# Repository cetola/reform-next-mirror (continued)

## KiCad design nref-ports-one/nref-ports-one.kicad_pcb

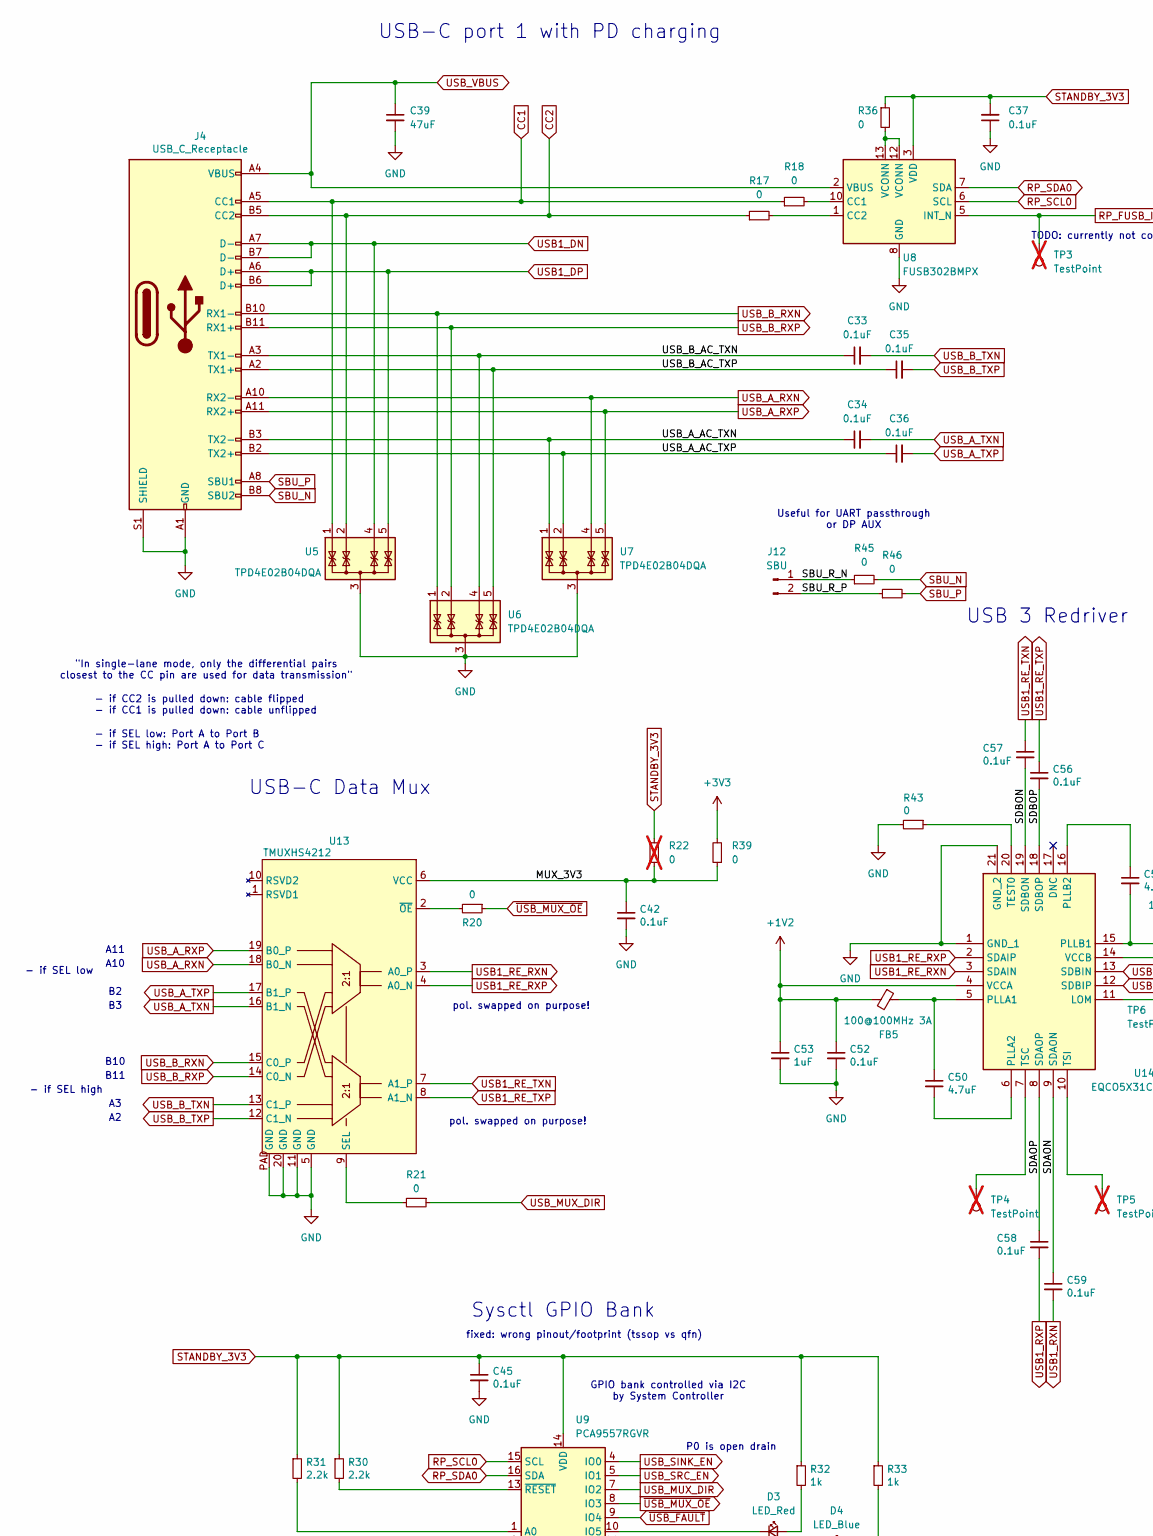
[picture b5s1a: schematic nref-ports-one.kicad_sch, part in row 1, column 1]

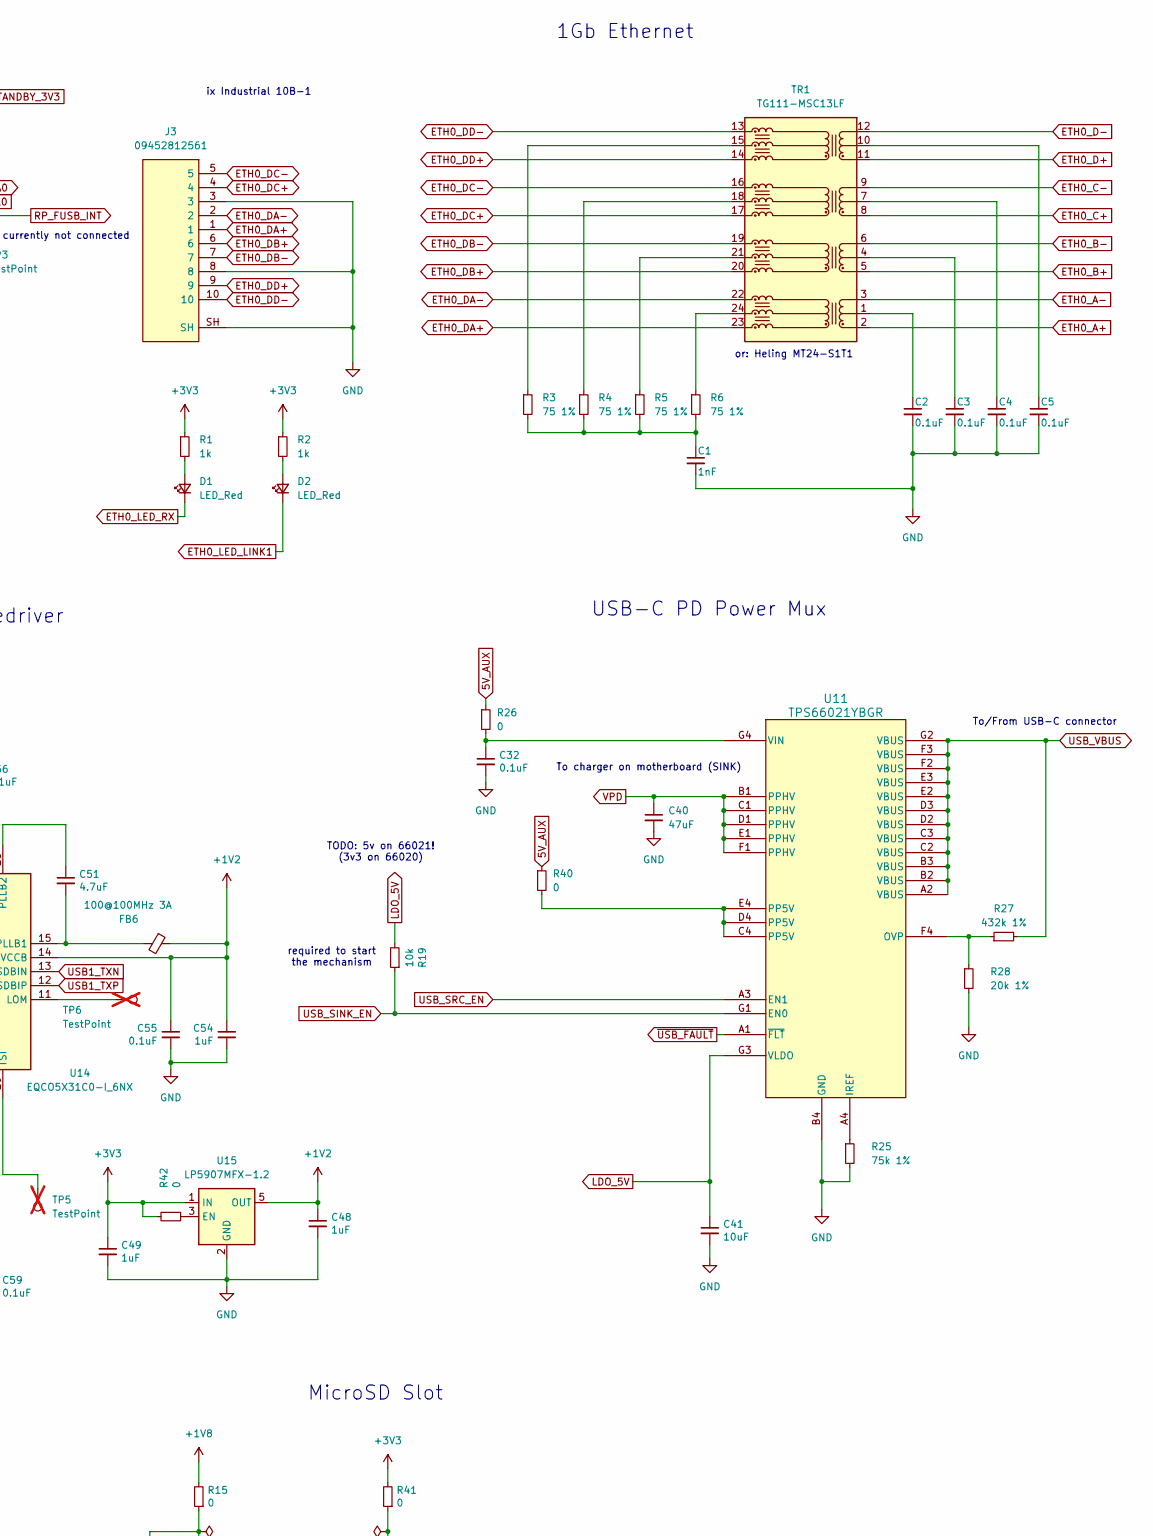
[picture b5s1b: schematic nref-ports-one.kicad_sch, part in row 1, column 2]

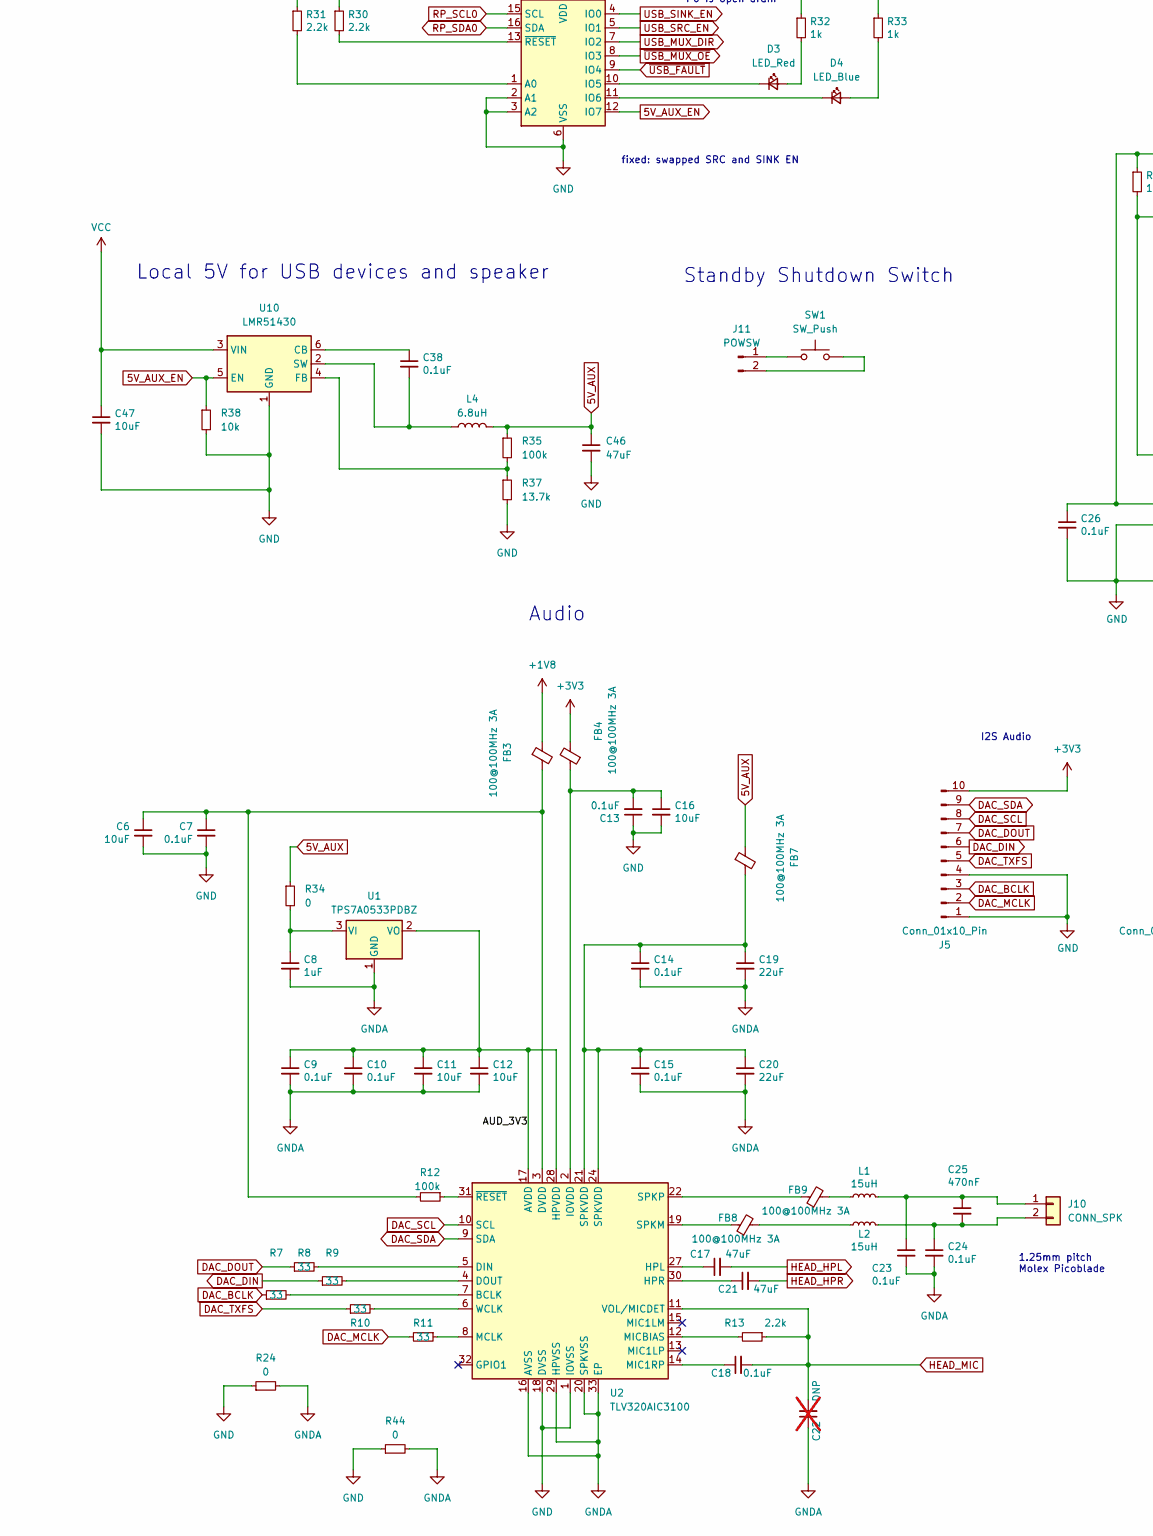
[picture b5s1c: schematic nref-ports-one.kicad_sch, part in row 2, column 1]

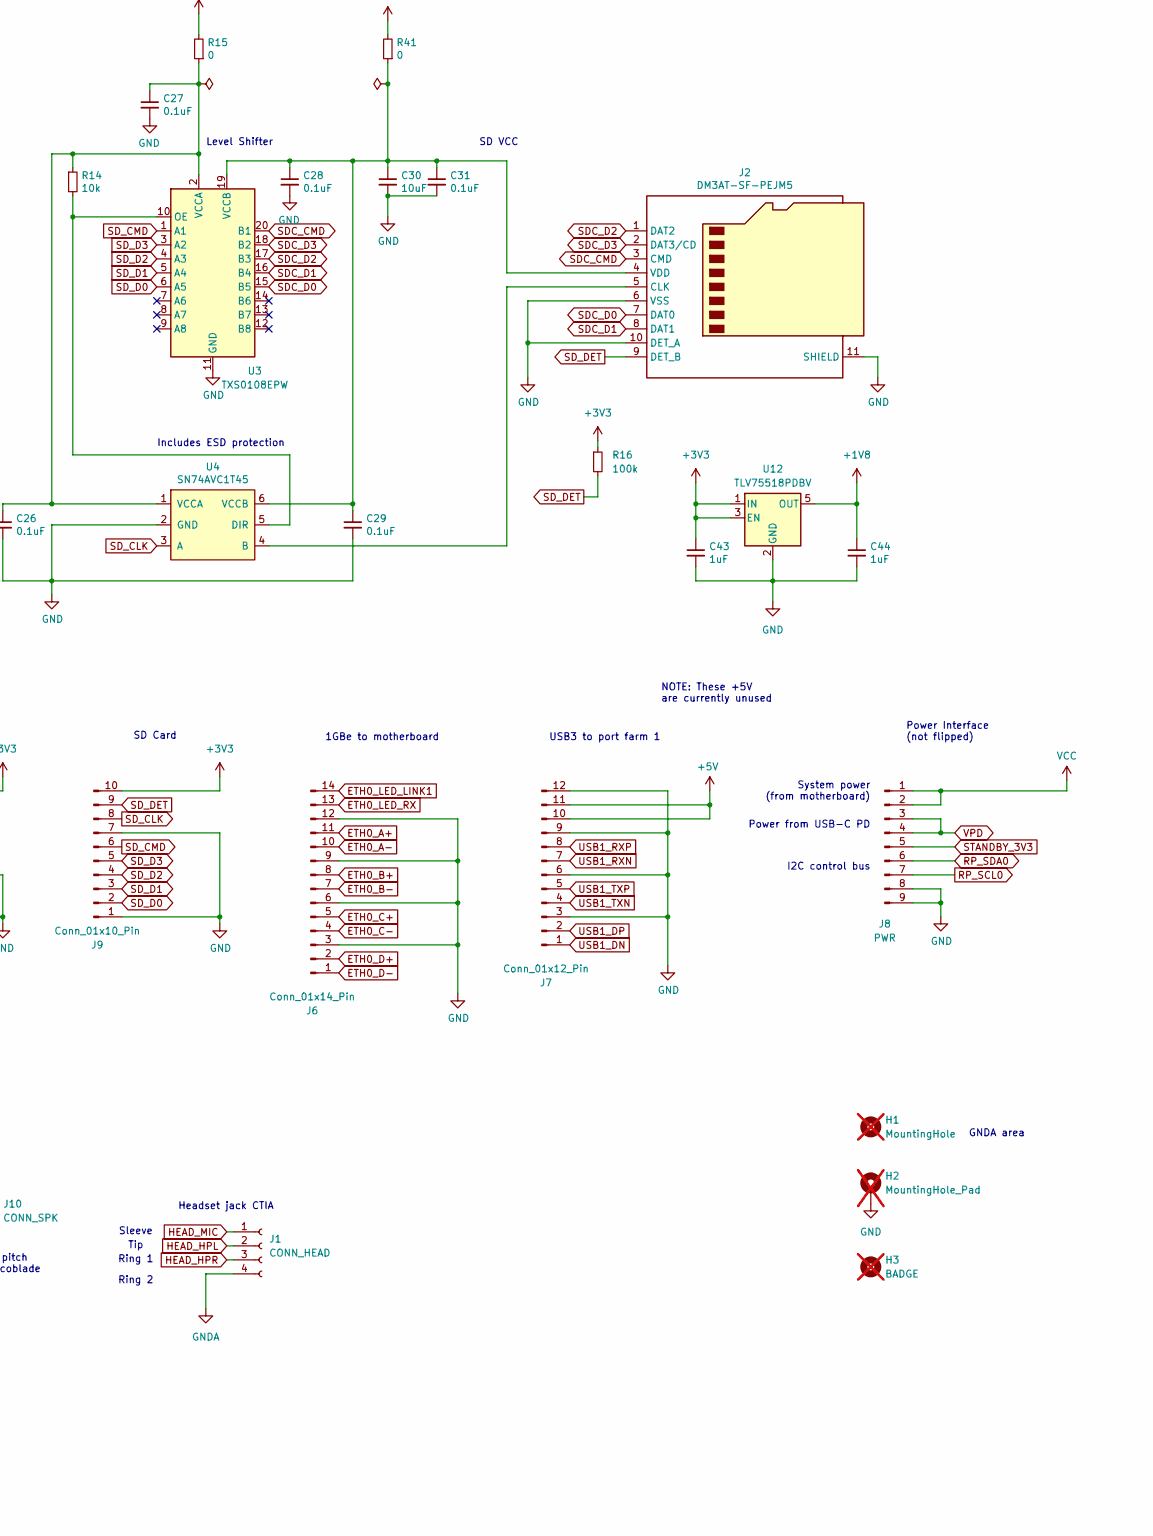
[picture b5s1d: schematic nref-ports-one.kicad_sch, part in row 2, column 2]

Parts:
C1: 1nF; C_0402_1005Metric; LCSC C1523
C2, C3, C4, C5, C7, C9, C10, C13, C14, C15, C18, C23, C24, C26, C27, C28, C29, C31, C32, C33, C34, C35, C36, C37, C38, C42, C45, C52, C55, C56, C57, C58, C59: 0.1uF; C_0402_1005Metric; LCSC C1525
C6, C11, C12, C16, C30, C41, C47: 10uF; C_0603_1608Metric; LCSC C96446
C8, C43, C44, C48, C49, C53, C54: 1uF; C_0402_1005Metric; LCSC C52923
C17, C21, C39, C40, C46: 47uF; C_1210_3225Metric; LCSC C90142
C19, C20: 22uF; C_0805_2012Metric; LCSC C29277
C22: DNP; C_0402_1005Metric; LCSC C1525; not fitted
C25: 470nF; C_0402_1005Metric; LCSC C47339
C50, C51: 4.7uF; C_0402_1005Metric; LCSC C307423
D1, D2, D3: LED_Red; LED_0603_1608Metric; LCSC C965799
D4: LED_Blue; LED_0603_1608Metric; LCSC C965807
FB3, FB4, FB5, FB6, FB7, FB8, FB9: 100@100MHz 3A; L_0402_1005Metric; LCSC C76891
H1: MountingHole; MountingHole_2.2mm_M2; not fitted
H2: MountingHole_Pad; MountingHole_2.2mm_M2_Pad; not fitted
H3: BADGE; nref-ports-one-badge; not fitted
J1: CONN_HEAD; CUI_SJ-43614-SMT; LCSC C4992770
J2: DM3AT-SF-PEJM5; microSD_HC_Hirose_DM3AT-SF-PEJM5; LCSC C114218
J3: 09452812561; LCSC C19193264
J4: USB_C_Receptacle; USB_C_Receptacle_Molex_105450-0101; LCSC C134092
J5, J9: Conn_01x10_Pin; Hirose_FH12-10S-0.5SH_1x10-1MP_P0.50mm_Horizontal; LCSC C506791
J6: Conn_01x14_Pin; Hirose_FH12-14S-0.5SH_1x14-1MP_P0.50mm_Horizontal; LCSC C5378715
J7: Conn_01x12_Pin; Hirose_FH12-12S-0.5SH_1x12-1MP_P0.50mm_Horizontal; LCSC C88360
J8: PWR; JST_SH_SM09B-SRSS-TB_1x09-1MP_P1.00mm_Horizontal; LCSC C160408
J10: CONN_SPK; Molex_PicoBlade_53261-0271_1x02-1MP_P1.25mm_Horizontal; LCSC C177225
J11: POWSW; JST_SH_SM02B-SRSS-TB_1x02-1MP_P1.00mm_Horizontal; LCSC C160402
J12: SBU; JST_SH_SM02B-SRSS-TB_1x02-1MP_P1.00mm_Horizontal; LCSC C160402
L1, L2: 15uH; L_Taiyo-Yuden_NR-30xx; LCSC C497563
L4: 6.8uH; L_Taiyo-Yuden_NR-30xx; LCSC C7423322
R1, R2, R32, R33: 1k; R_0402_1005Metric; LCSC C11702
R3, R4, R5, R6: 75 1%; R_0402_1005Metric; LCSC C413061
R7, R8, R9, R10, R11: 33; R_0402_1005Metric; LCSC C25105
R12, R16, R35: 100k; R_0402_1005Metric; LCSC C25741
R13, R30, R31: 2.2k; R_0402_1005Metric; LCSC C25879
R14, R19, R38: 10k; R_0402_1005Metric; LCSC C25744
R15, R17, R18, R20, R21, R24, R26, R34, R36, R39, R41, R42, R43, R44, R45, R46: 0; R_0402_1005Metric; LCSC C17168
R22: 0; R_0402_1005Metric; LCSC C17168; not fitted
R25: 75k 1%; R_0402_1005Metric; LCSC C25798
R27: 432k 1%; R_0402_1005Metric; LCSC C227078
R28: 20k 1%; R_0402_1005Metric; LCSC C93942
R37: 13.7k; R_0402_1005Metric; LCSC C25854
R40: 0; R_0603_1608Metric; LCSC C21189
SW1: SW_Push; SW_SPST_B3U-3000P; LCSC C963349
TP3, TP4, TP5, TP6: TestPoint; TestPoint_Pad_D1.0mm; not fitted
TR1: TG111-MSC13LF; Transformer_Ethernet_HALO_TG111-MSC13; LCSC C501477
U1: TPS7A0533PDBZ; SOT-23; LCSC C42411811
U2: TLV320AIC3100; VQFN-32-1EP_5x5mm_P0.5mm_EP3.5x3.5mm; LCSC C478458
U3: TXS0108EPW; TSSOP-20_4.4x6.5mm_P0.65mm; LCSC C17206
U4: SN74AVC1T45; SOT-23-6; LCSC C131978
U5, U6, U7: TPD4E02B04DQA; USON-10_2.5x1.0mm_P0.5mm; LCSC C2841426
U8: FUSB302BMPX; WQFN-14-1EP_2.5x2.5mm_P0.5mm_EP1.45x1.45mm; LCSC C132291
U9: PCA9557RGVR; Texas_RSA_VQFN-16-1EP_4x4mm_P0.65mm_EP2.7x2.7mm; LCSC C2669728
U10: LMR51430; SOT-23-6; LCSC C5185863
U11: TPS66021YBGR; YBG0028_TEX; LCSC C1855766
U12: TLV75518PDBV; SOT-23-5; LCSC C2877863
U13: TMUXHS4212; Texas-VQFN20_2.5x4.5mm_RKS; MPN TMUXHS4212RKSR; LCSC C2869871
U14: EQCO5X31C0-I_6NX; QFN50P400X400X100-21N-D; Mouser Part Number 494-EQCO5X31C0-I/6NX
U15: LP5907MFX-1.2; SOT-23-5; LCSC C73478

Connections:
5V_AUX: C46.1, FB7.1, L4.2, R26.1, R34.1, R35.1, R40.1
5V_AUX_EN: R38.1, U9.12 (IO7), U10.5 (EN)
+1V2: C48.1, C52.1, C53.1, C54.1, C55.1, FB5.2, FB6.1, U14.4 (VCCA), U14.14 (VCCB), U15.5 (OUT)
+1V8: C44.1, FB3.1, R15.2, U12.5 (OUT)
+3V3: C43.1, C49.1, FB4.2, J5.10, J9.10, R1.1, R2.1, R16.1, R39.2, R41.2, R42.2, U12.1 (IN), U12.3 (EN), U15.1 (IN)
+5V: J7.10, J7.11
/AUD_3V3: C9.1, C10.1, C11.1, C12.1, U1.2 (VO), U2.17 (AVDD), U2.28 (HPVDD)
/MUX_3V3: C42.1, R22.1, R39.1, U13.6 (VCC)
/SBU_R_N: J12.1, R45.1
/SBU_R_P: J12.2, R46.1
/SDAON: C59.1, U14.9 (SDAON)
/SDAOP: C58.1, U14.8 (SDAOP)
/SDBON: C57.2, U14.19 (SDBON)
/SDBOP: C56.2, U14.18 (SDBOP)
/USB_A_AC_TXN: C34.1, J4.B3 (TX2-), U7.1 (IO1), U7.10 (IO1)
/USB_A_AC_TXP: C36.1, J4.B2 (TX2+), U7.2 (IO2), U7.9 (IO2)
/USB_B_AC_TXN: C33.1, J4.A3 (TX1-), U6.4 (IO3), U6.7 (IO3)
/USB_B_AC_TXP: C35.1, J4.A2 (TX1+), U6.5 (IO4), U6.6 (IO4)
CC1: J4.A5 (CC1), R18.1, U5.1 (IO1), U5.10 (IO1)
CC2: J4.B5 (CC2), R17.1, U5.2 (IO2), U5.9 (IO2)
DAC_BCLK: J5.3, R7.1
DAC_DIN: J5.6, R9.1
DAC_DOUT: J5.7, R8.1
DAC_MCLK: J5.2, R11.2
DAC_SCL: J5.8, U2.10 (SCL)
DAC_SDA: J5.9, U2.9 (SDA)
DAC_TXFS: J5.5, R10.1
ETH0_A+: J6.11, TR1.2 (TD1+)
ETH0_A-: J6.10, TR1.3 (TD1-)
ETH0_B+: J6.8, TR1.5 (TD2+)
ETH0_B-: J6.7, TR1.6 (TD2-)
ETH0_C+: J6.5, TR1.8 (TD3+)
ETH0_C-: J6.4, TR1.9 (TD3-)
ETH0_D+: J6.2, TR1.11 (TD4+)
ETH0_D-: J6.1, TR1.12 (TD4-)
ETH0_DA+: J3.1, TR1.23 (MTX1+)
ETH0_DA-: J3.2, TR1.22 (MTX1-)
ETH0_DB+: J3.6, TR1.20 (MTX2+)
ETH0_DB-: J3.7, TR1.19 (MTX2-)
ETH0_DC+: J3.4, TR1.17 (MTX3+)
ETH0_DC-: J3.5, TR1.16 (MTX3-)
ETH0_DD+: J3.9, TR1.14 (MX4+)
ETH0_DD-: J3.10, TR1.13 (MX4-)
ETH0_LED_LINK1: D2.1 (K), J6.14
ETH0_LED_RX: D1.1 (K), J6.13
GND: C1.2, C2.2, C3.2, C4.2, C5.2, C6.2, C7.2, C13.1, C16.2, C26.2, C27.2, C28.2, C29.2, C30.2, C31.2, C32.2, C37.1, C39.2, C40.2, C41.2, C42.2, C43.2, C44.2, C45.2, C46.2, C47.2, C48.2, C49.2, C52.2, C53.2, C54.2, C55.2, H2.1, J2.6 (VSS), J2.10 (DET_A), J2.11 (SHIELD), J3.3, J3.8, J3.SH, J4.A1 (GND), J4.A12 (GND), J4.B1 (GND), J4.B12 (GND), J4.S1 (SHIELD), J5.1, J5.4, J6.3, J6.6, J6.9, J6.12, J7.3, J7.6, J7.9, J7.12, J8.8, J8.9, J9.1, J9.7, R24.1, R25.2, R28.2, R37.2, R38.2, R43.2, R44.1, U2.1 (IOVSS), U2.18 (DVSS), U3.11 (GND), U4.2 (GND), U5.3 (G), U5.8 (G), U6.3 (G), U6.8 (G), U7.3 (G), U7.8 (G), U8.8 (GND), U8.9 (GND), U8.15 (GND), U9.2 (A1), U9.3 (A2), U9.6 (VSS), U10.1 (GND), U11.B4 (GND), U12.2 (GND), U13.5 (GND), U13.11 (GND), U13.20 (GND), U13.PAD (GND), U14.1 (GND_1), U14.21 (GND_2), U15.2 (GND)
GNDA: C8.2, C9.2, C10.2, C11.2, C12.2, C14.2, C15.2, C19.2, C20.2, C22.1, C23.2, C24.2, J1.4, R24.2, R44.2, U1.1 (GND), U2.16 (AVSS), U2.20 (SPKVSS), U2.25 (SPKVSS), U2.29 (HPVSS), U2.33 (EP)
HEAD_HPL: C17.2, J1.2
HEAD_HPR: C21.2, J1.3
HEAD_MIC: C18.2, C22.2, J1.1, R13.1, U2.11 (VOL/MICDET)
LDO_5V: C41.1, R19.2, U11.G3 (VLDO)
unnamed: C1.1, R3.2, R4.2, R5.2, R6.2
unnamed: C14.1, C15.1, C19.1, C20.1, FB7.2, U2.21 (SPKVDD), U2.24 (SPKVDD)
unnamed: D1.2 (A), R1.2
unnamed: D2.2 (A), R2.2
unnamed: D3.2 (A), R32.2
unnamed: D3.1 (K), U9.10 (IO5)
unnamed: D4.2 (A), R33.2
unnamed: D4.1 (K), U9.11 (IO6)
unnamed: FB8.1, U2.19 (SPKM), U2.23 (SPKM)
unnamed: FB8.2, L2.1
unnamed: FB9.1, U2.22 (SPKP), U2.26 (SPKP)
unnamed: FB9.2, L1.1
unnamed: J2.5 (CLK), U4.4 (B)
unnamed: C28.1, C29.1, C30.1, C31.1, J2.4 (VDD), R41.1, U3.19 (VCCB), U4.6 (VCCB)
unnamed: C23.1, C25.1, J10.1, L1.2
unnamed: C24.1, C25.2, J10.2, L2.2
unnamed: J11.1, SW1.1
unnamed: J11.2, SW1.2
unnamed: R17.2, U8.1 (CC2), U8.14 (CC2)
unnamed: R18.2, U8.10 (CC1), U8.11 (CC1)
unnamed: R36.2, U8.12 (VCONN), U8.13 (VCONN)
unnamed: R40.2, U11.C4 (PP5V), U11.D4 (PP5V), U11.E4 (PP5V)
unnamed: R5.1, TR1.21 (MCT2)
unnamed: R4.1, TR1.18 (MCT3)
unnamed: R3.1, TR1.15 (MCT4)
unnamed: R6.1, TR1.24 (MTC1)
unnamed: C2.1, TR1.1 (TCT1)
unnamed: C3.1, TR1.4 (TCT2)
unnamed: C4.1, TR1.7 (TCT3)
unnamed: C5.1, TR1.10 (TCT4)
unnamed: C8.1, R34.2, U1.3 (VI)
unnamed: R7.2, U2.7 (BCLK)
unnamed: R8.2, U2.5 (DIN)
unnamed: R9.2, U2.4 (DOUT)
unnamed: C6.1, C7.1, FB3.2, R12.2, U2.3 (DVDD)
unnamed: C17.1, U2.27 (HPL)
unnamed: C21.1, U2.30 (HPR)
unnamed: C13.2, C16.1, FB4.1, U2.2 (IOVDD)
unnamed: R11.1, U2.8 (MCLK)
unnamed: C18.1, U2.14 (MIC1RP)
unnamed: R13.2, U2.12 (MICBIAS)
unnamed: R10.2, U2.6 (WCLK)
unnamed: R12.1, U2.31 (~RESET)
unnamed: R14.2, U3.10 (OE), U4.5 (DIR)
unnamed: C26.1, C27.1, R14.1, R15.1, U3.2 (VCCA), U4.1 (VCCA)
unnamed: R31.2, U9.1 (A0)
unnamed: R30.2, U9.13 (~RESET)
unnamed: C38.1, U10.6 (CB)
unnamed: R35.2, R37.1, U10.4 (FB)
unnamed: C38.2, L4.1, U10.2 (SW)
unnamed: R25.1, U11.A4 (IREF)
unnamed: R27.1, R28.1, U11.F4 (OVP)
unnamed: C32.1, R26.2, U11.G4 (VIN)
unnamed: R21.2, U13.9 (SEL)
unnamed: R20.2, U13.2 (~OE)
unnamed: TP6.1, U14.11 (LOM)
unnamed: C50.1, FB5.1, U14.5 (PLLA1)
unnamed: C50.2, U14.6 (PLLA2)
unnamed: C51.2, FB6.2, U14.15 (PLLB1)
unnamed: C51.1, U14.16 (PLLB2)
unnamed: R43.1, U14.20 (TEST0)
unnamed: TP4.1, U14.7 (TSC)
unnamed: TP5.1, U14.10 (TSI)
unnamed: R42.1, U15.3 (EN)
RP_FUSB_INT: TP3.1, U8.5 (INT_N)
RP_SCL0: J8.7, U8.6 (SCL), U9.15 (SCL)
RP_SDA0: J8.6, U8.7 (SDA), U9.16 (SDA)
SBU_N: J4.B8 (SBU2), R45.2
SBU_P: J4.A8 (SBU1), R46.2
SDC_CMD: J2.3 (CMD), U3.20 (B1)
SDC_D0: J2.7 (DAT0), U3.15 (B5)
SDC_D1: J2.8 (DAT1), U3.16 (B4)
SDC_D2: J2.1 (DAT2), U3.17 (B3)
SDC_D3: J2.2 (DAT3/CD), U3.18 (B2)
SD_CLK: J9.8, U4.3 (A)
SD_CMD: J9.6, U3.1 (A1)
SD_D0: J9.2, U3.6 (A5)
SD_D1: J9.3, U3.5 (A4)
SD_D2: J9.4, U3.4 (A3)
SD_D3: J9.5, U3.3 (A2)
SD_DET: J2.9 (DET_B), J9.9, R16.2
STANDBY_3V3: C37.2, C45.1, J8.5, R22.2, R30.1, R31.1, R32.1, R33.1, R36.1, U8.3 (VDD), U8.4 (VDD), U9.14 (VDD)
USB1_DN: J4.A7 (D-), J4.B7 (D-), J7.1, U5.4 (IO3), U5.7 (IO3)
USB1_DP: J4.A6 (D+), J4.B6 (D+), J7.2, U5.5 (IO4), U5.6 (IO4)
USB1_RE_RXN: U13.3 (A0_P), U14.3 (SDAIN)
USB1_RE_RXP: U13.4 (A0_N), U14.2 (SDAIP)
USB1_RE_TXN: C57.1, U13.7 (A1_P)
USB1_RE_TXP: C56.1, U13.8 (A1_N)
USB1_RXN: C59.2, J7.7
USB1_RXP: C58.2, J7.8
USB1_TXN: J7.4, U14.13 (SDBIN)
USB1_TXP: J7.5, U14.12 (SDBIP)
USB_A_RXN: J4.A10 (RX2-), U7.4 (IO3), U7.7 (IO3), U13.18 (B0_N)
USB_A_RXP: J4.A11 (RX2+), U7.5 (IO4), U7.6 (IO4), U13.19 (B0_P)
USB_A_TXN: C34.2, U13.16 (B1_N)
USB_A_TXP: C36.2, U13.17 (B1_P)
USB_B_RXN: J4.B10 (RX1-), U6.1 (IO1), U6.10 (IO1), U13.15 (C0_P)
USB_B_RXP: J4.B11 (RX1+), U6.2 (IO2), U6.9 (IO2), U13.14 (C0_N)
USB_B_TXN: C33.2, U13.13 (C1_P)
USB_B_TXP: C35.2, U13.12 (C1_N)
USB_MUX_DIR: R21.1, U9.7 (IO2)
USB_SINK_EN: R19.1, U9.4 (IO0), U11.G1 (EN0)
USB_SRC_EN: U9.5 (IO1), U11.A3 (EN1)
USB_VBUS: C39.1, J4.A4 (VBUS), J4.A9 (VBUS), J4.B4 (VBUS), J4.B9 (VBUS), R27.2, U8.2 (VBUS), U11.A2 (VBUS), U11.B2 (VBUS), U11.B3 (VBUS), U11.C2 (VBUS), U11.C3 (VBUS), U11.D2 (VBUS), U11.D3 (VBUS), U11.E2 (VBUS), U11.E3 (VBUS), U11.F2 (VBUS), U11.F3 (VBUS), U11.G2 (VBUS)
VCC: C47.1, J8.1, J8.2, U10.3 (VIN)
VPD: C40.1, J8.3, J8.4, U11.B1 (PPHV), U11.C1 (PPHV), U11.D1 (PPHV), U11.E1 (PPHV), U11.F1 (PPHV)
~USB_FAULT: U9.9 (IO4), U11.A1 (~FLT)
~USB_MUX_OE: R20.1, U9.8 (IO3)

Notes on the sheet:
1Gb Ethernet
required to start the mechanism
"In single-lane mode, only the differential pairs closest to the CC pin are used for data transmission"
TODO: 5v on 66021! (3v3 on 66020)
Power from USB-C PD
B10
Includes ESD protection
- if SEL low: Port A to Port B - if SEL high: Port A to Port C
GPIO bank controlled via I2C by System Controller
Standby Shutdown Switch
or: Heling MT24-S1T1
NOTE: These +5V are currently unused
USB-C port 1 with PD charging
Local 5V for USB devices and speaker
1GBe to motherboard
B11
1.25mm pitch Molex Picoblade
- if SEL high
Ring 1
Useful for UART passthrough or DP AUX
Audio
To/From USB-C connector
Sleeve
P0 is open drain
USB-C Data Mux
GNDA area
SD VCC
fixed: swapped SRC and SINK EN
TODO: currently not connected
SD Card
USB-C PD Power Mux
A10
Headset jack CTIA
Tip
- if CC2 is pulled down: cable flipped - if CC1 is pulled down: cable unflipped
Power Interface (not flipped)
Ring 2
pol. swapped on purpose!
Sysctl GPIO Bank
I2S Audio

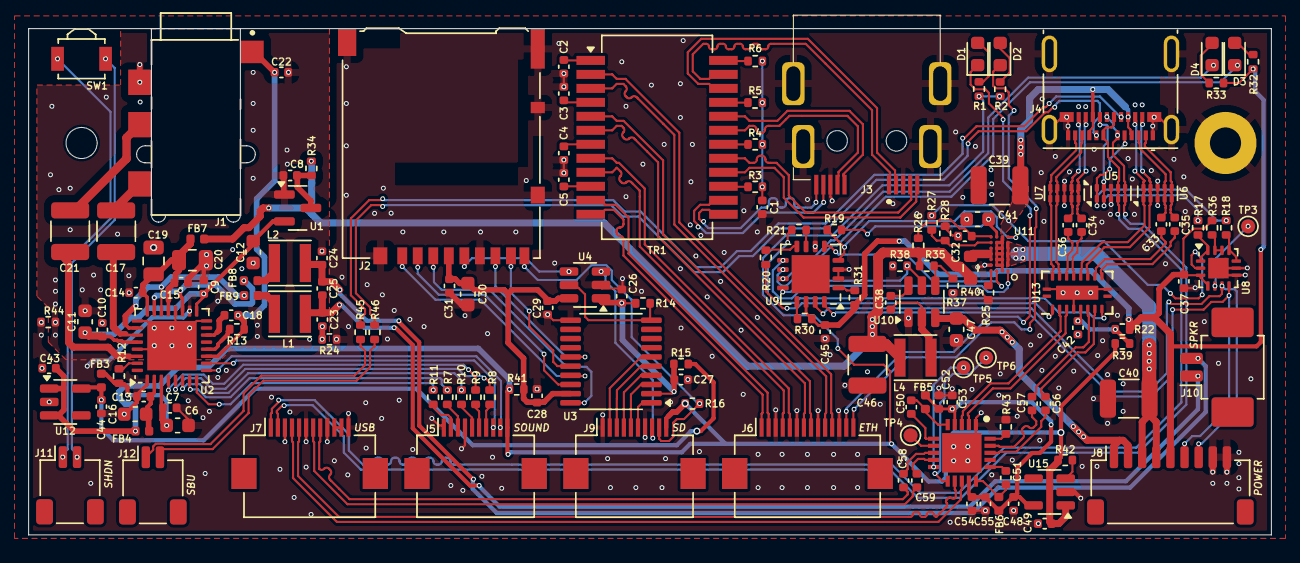
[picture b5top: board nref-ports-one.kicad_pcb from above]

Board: 4 copper layers, 88.0 x 35.8 mm, 153 parts (1 on the bottom side), 159 nets.
